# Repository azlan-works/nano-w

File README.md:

# nano-w
A tiny RP2354A based dev board with WiFi and BLE

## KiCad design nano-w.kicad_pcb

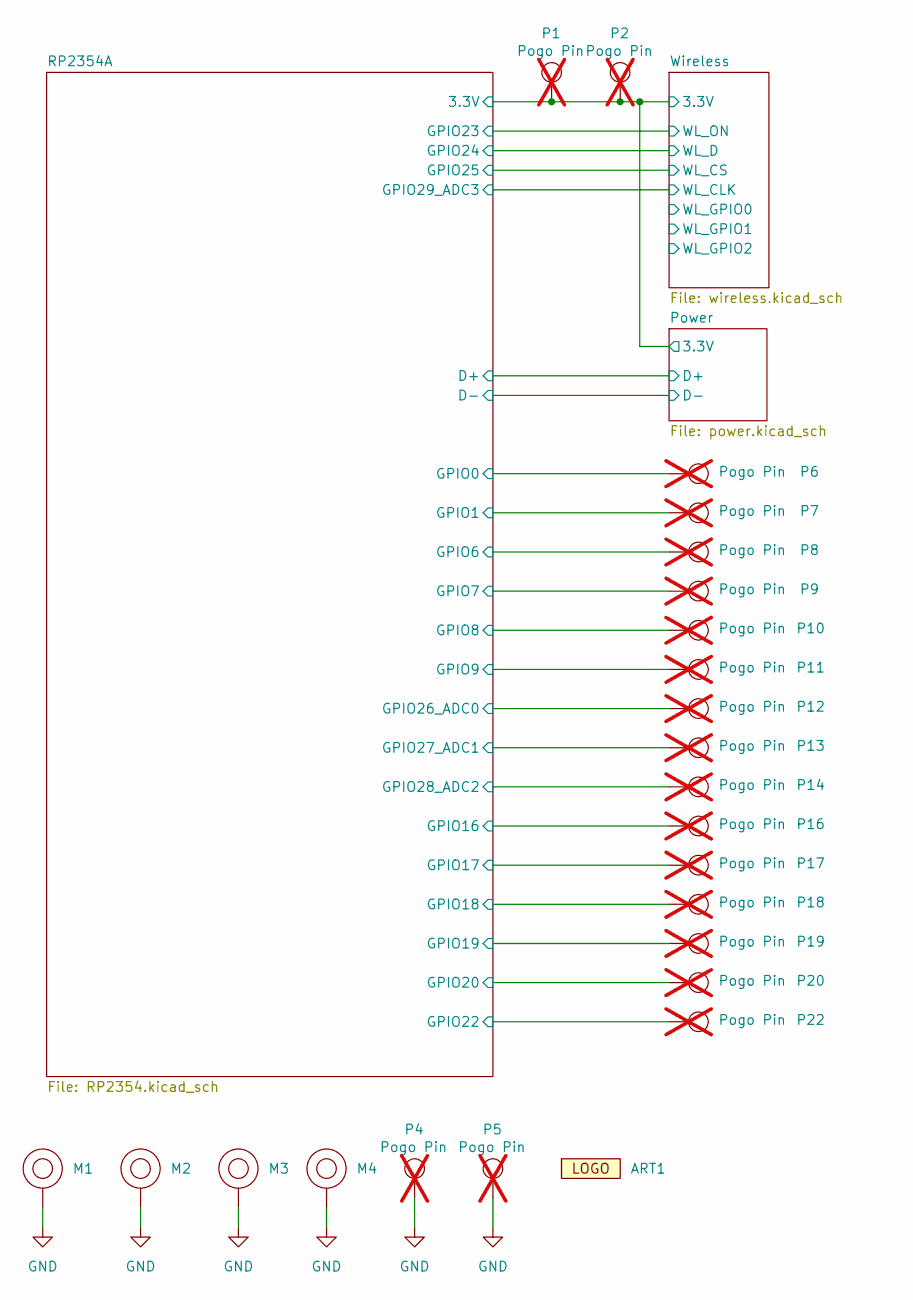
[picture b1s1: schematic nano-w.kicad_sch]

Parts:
ART1: azlan.works_logo
M1, M2, M3, M4: M2_Hole
P1, P2, P4, P5, P6, P7, P8, P9, P10, P11, P12, P13, P14, P16, P17, P18, P19, P20, P22: Pogo Pin; TESTPOINT-SMD_BD2.0_C9900030651; MPN YTC1P-3010-01; LCSC Part C5221282; not fitted

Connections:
+3V3: P1.1 (1_1), P2.1 (1_1); also elsewhere on the board
/RP2354A/GPIO6: P8.1 (1_1); also elsewhere on the board
/RP2354A/GPIO7: P9.1 (1_1); also elsewhere on the board
/RP2354A/GPIO8: P10.1 (1_1); also elsewhere on the board
/RP2354A/GPIO9: P11.1 (1_1); also elsewhere on the board
/RP2354A/GPIO16: P16.1 (1_1); also elsewhere on the board
/RP2354A/GPIO17: P17.1 (1_1); also elsewhere on the board
/RP2354A/GPIO18: P18.1 (1_1); also elsewhere on the board
/RP2354A/GPIO19: P19.1 (1_1); also elsewhere on the board
/RP2354A/GPIO20: P20.1 (1_1); also elsewhere on the board
/RP2354A/GPIO22: P22.1 (1_1); also elsewhere on the board
/RP2354A/GPIO26_ADC0: P12.1 (1_1); also elsewhere on the board
/RP2354A/GPIO27_ADC1: P13.1 (1_1); also elsewhere on the board
/RP2354A/GPIO28_ADC2: P14.1 (1_1); also elsewhere on the board
GND: M1.1 (1_1), M2.1 (1_1), M3.1 (1_1), M4.1 (1_1), P4.1 (1_1), P5.1 (1_1); also elsewhere on the board

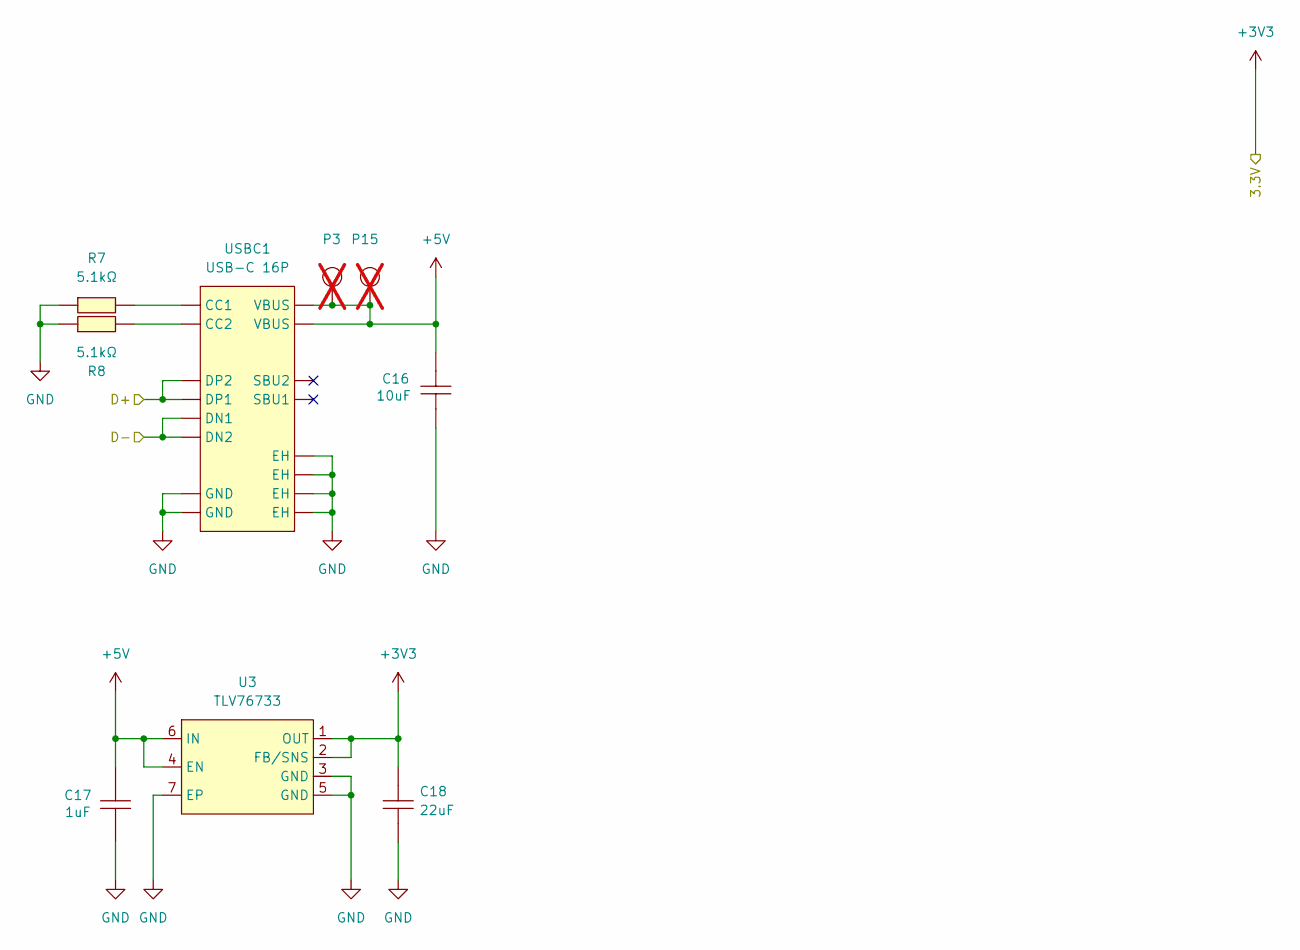
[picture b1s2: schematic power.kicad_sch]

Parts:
C16: 10uF; C0603; MPN CL10A106MA8NRNC; LCSC Part C96446
C17: 1uF; C0603; MPN CL10A105KB8NNNC; LCSC Part C15849
C18: 22uF; C0603; MPN CL10A226MQ8NRNC; LCSC Part C59461
P3, P15: Pogo Pin; TESTPOINT-SMD_BD2.0_C9900030651; MPN YTC1P-3010-01; LCSC Part C5221282; not fitted
R7, R8: 5.1kΩ; R0402; MPN 0402WGF5101TCE; LCSC Part C25905
U3: TLV76733; WSON-6_L2.0-W2.0-P0.65-TL-EP; MPN TLV76733DRVR; LCSC Part C2848334
USBC1: USB-C 16P; USB-C_SMD-TYPE-C-31-M-12_1; MPN TYPE-C-31-M-12; LCSC Part C165948

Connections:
+3V3: C18.2, U3.1 (OUT), U3.2 (FB/SNS); also elsewhere on the board
+5V: C16.2, C17.2, P3.1 (1_1), P15.1 (1_1), U3.4 (EN), U3.6 (IN), USBC1.A4B9 (VBUS), USBC1.B4A9 (VBUS)
/Power/D+: USBC1.A6 (DP1), USBC1.B6 (DP2); also elsewhere on the board
/Power/D-: USBC1.A7 (DN1), USBC1.B7 (DN2); also elsewhere on the board
GND: C16.1, C17.1, C18.1, R7.1, R8.1, U3.3 (GND), U3.5 (GND), U3.7 (EP), USBC1.1 (EH), USBC1.2 (EH), USBC1.3 (EH), USBC1.4 (EH), USBC1.A1B12 (GND), USBC1.B1A12 (GND); also elsewhere on the board
unnamed: R7.2, USBC1.A5 (CC1)
unnamed: R8.2, USBC1.B5 (CC2)

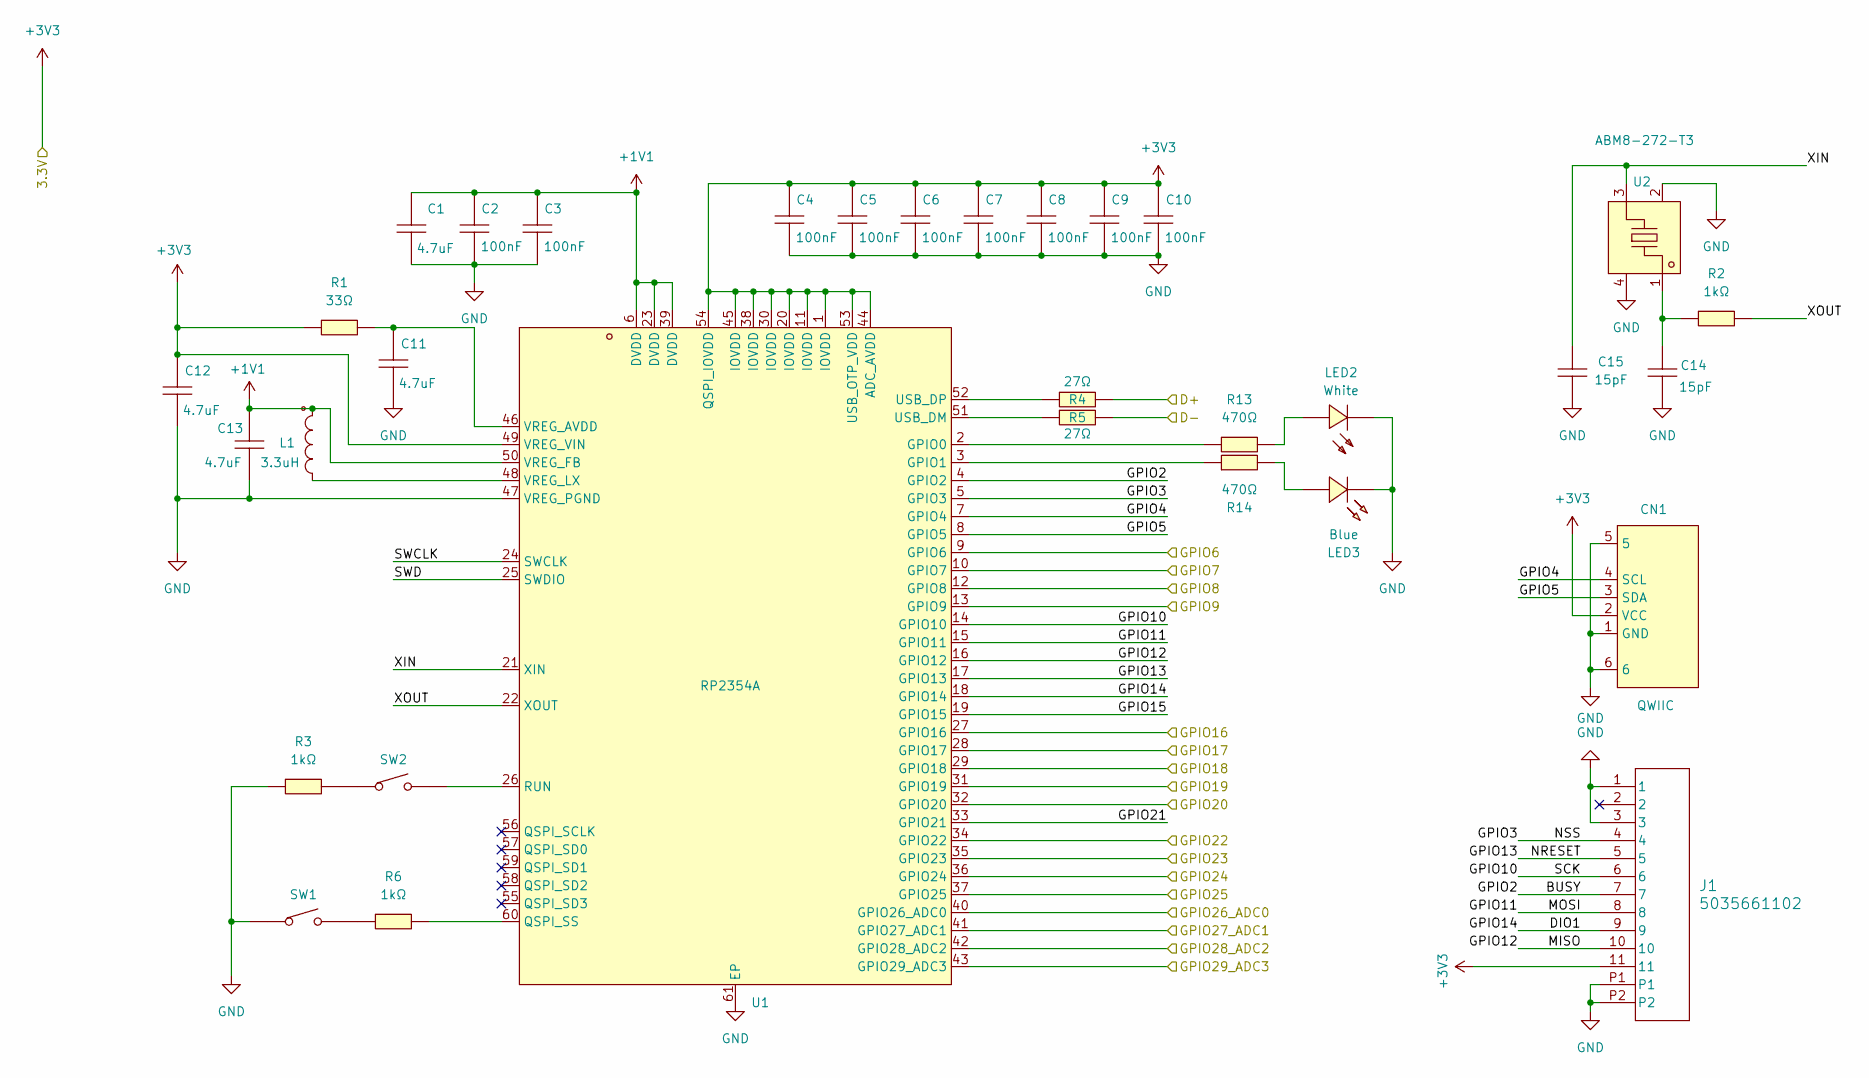
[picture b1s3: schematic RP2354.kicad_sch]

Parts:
C1, C11: 4.7uF; C0402; MPN CL05A475MP5NRNC; LCSC Part C23733
C2, C3, C4, C5, C6, C7, C8, C9, C10: 100nF; C0402; MPN CL05B104KB54PNC; LCSC Part C307331
C12, C13: 4.7uF; C0402_WIDE; MPN CL05A475MP5NRNC; LCSC Part C23733
C14, C15: 15pF; C0402; MPN 0402CG150J500NT; LCSC Part C1548
CN1: QWIIC; CONN-SMD_4P-P1.00_SM04B-SRSS-TB-LF-SN; MPN SM04B-SRSS-TB(LF)(SN); LCSC Part C160404
J1: 5035661102; CON_5035661102_MOL; MPN 503566-1102; LCSC Part C3036270
L1: 3.3uH; IND-SMD_L2.0-W1.6_AOTA-B201610S3R3-101-T; MPN AOTA-B201610S3R3-101-T; LCSC Part C42411119
LED2: White; LED-SMD_L1.0-W0.5-RD_WHITE; MPN LTW-C281DS5; LCSC Part C157742
LED3: Blue; LED0402-RD_BLUE; MPN LTST-C281TBKT-5A; LCSC Part C364550
R1: 33Ω; R0402; MPN 0402WGF330JTCE; LCSC Part C25105
R2, R3, R6: 1kΩ; R0402; MPN 0402WGF1001TCE; LCSC Part C11702
R4, R5: 27Ω; R0402; MPN 0402WGF270JTCE; LCSC Part C25100
R13, R14: 470Ω; R0402; MPN 0402WGF4700TCE; LCSC Part C25117
SW1, SW2: Button; SW-SMD_L3.9-W3.0-P4.45; MPN TS-1088-AR02016; LCSC Part C720477
U1: RP2354A; QFN-60_L7.0-W7.0-P0.40-TL-EP3.4; MPN RP2354A; LCSC Part C41378174
U2: ABM8-272-T3; CRYSTAL-SMD_4P-L3.2-W2.5-BL; MPN ABM8-272-T3; LCSC Part C20625731

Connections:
+1V1: C1.2, C2.2, C3.2, C13.2, L1.1, U1.6 (DVDD), U1.23 (DVDD), U1.39 (DVDD), U1.50 (VREG_FB)
+3V3: C4.2, C5.2, C6.2, C7.2, C8.2, C9.2, C10.2, C12.2, CN1.2 (VCC), J1.11, R1.1, U1.1 (IOVDD), U1.11 (IOVDD), U1.20 (IOVDD), U1.30 (IOVDD), U1.38 (IOVDD), U1.44 (ADC_AVDD), U1.45 (IOVDD), U1.49 (VREG_VIN), U1.53 (USB_OTP_VDD), U1.54 (QSPI_IOVDD); also elsewhere on the board
/Power/D+: R4.2; also elsewhere on the board
/Power/D-: R5.2; also elsewhere on the board
/RP2354A/BUSY: J1.7, U1.4 (GPIO2)
/RP2354A/DIO1: J1.9, U1.18 (GPIO14)
/RP2354A/GPIO3: J1.4, U1.5 (GPIO3)
/RP2354A/GPIO4: CN1.4 (SCL), U1.7 (GPIO4)
/RP2354A/GPIO5: CN1.3 (SDA), U1.8 (GPIO5)
/RP2354A/GPIO6: U1.9 (GPIO6); also elsewhere on the board
/RP2354A/GPIO7: U1.10 (GPIO7); also elsewhere on the board
/RP2354A/GPIO8: U1.12 (GPIO8); also elsewhere on the board
/RP2354A/GPIO9: U1.13 (GPIO9); also elsewhere on the board
/RP2354A/GPIO10: J1.6, U1.14 (GPIO10)
/RP2354A/GPIO11: J1.8, U1.15 (GPIO11)
/RP2354A/GPIO12: J1.10, U1.16 (GPIO12)
/RP2354A/GPIO13: J1.5, U1.17 (GPIO13)
/RP2354A/GPIO15: U1.19 (GPIO15)
/RP2354A/GPIO16: U1.27 (GPIO16); also elsewhere on the board
/RP2354A/GPIO17: U1.28 (GPIO17); also elsewhere on the board
/RP2354A/GPIO18: U1.29 (GPIO18); also elsewhere on the board
/RP2354A/GPIO19: U1.31 (GPIO19); also elsewhere on the board
/RP2354A/GPIO20: U1.32 (GPIO20); also elsewhere on the board
/RP2354A/GPIO21: U1.33 (GPIO21)
/RP2354A/GPIO22: U1.34 (GPIO22); also elsewhere on the board
/RP2354A/GPIO23: U1.35 (GPIO23); also elsewhere on the board
/RP2354A/GPIO24: U1.36 (GPIO24); also elsewhere on the board
/RP2354A/GPIO25: U1.37 (GPIO25); also elsewhere on the board
/RP2354A/GPIO26_ADC0: U1.40 (GPIO26_ADC0); also elsewhere on the board
/RP2354A/GPIO27_ADC1: U1.41 (GPIO27_ADC1); also elsewhere on the board
/RP2354A/GPIO28_ADC2: U1.42 (GPIO28_ADC2); also elsewhere on the board
/RP2354A/GPIO29_ADC3: U1.43 (GPIO29_ADC3); also elsewhere on the board
/RP2354A/SWCLK: U1.24 (SWCLK)
/RP2354A/SWD: U1.25 (SWDIO)
/RP2354A/XIN: C15.1, U1.21 (XIN), U2.3
/RP2354A/XOUT: R2.2, U1.22 (XOUT)
GND: C1.1, C2.1, C3.1, C4.1, C5.1, C6.1, C7.1, C8.1, C9.1, C10.1, C11.1, C12.1, C13.1, C14.2, C15.2, CN1.1 (GND), CN1.5, CN1.6, J1.1, J1.3, J1.P1, J1.P2, LED2.1 (-), LED3.1 (K), R3.1, SW1.1, U1.47 (VREG_PGND), U1.61 (EP), U2.2 (GND), U2.4 (GND); also elsewhere on the board
unnamed: C14.1, R2.1, U2.1
unnamed: LED2.2 (+), R13.2
unnamed: LED3.2 (A), R14.2
unnamed: R3.2, SW2.1
unnamed: R6.1, SW1.2
unnamed: R13.1, U1.2 (GPIO0)
unnamed: R14.1, U1.3 (GPIO1)
unnamed: R6.2, U1.60 (QSPI_SS)
unnamed: SW2.2, U1.26 (RUN)
unnamed: R5.1, U1.51 (USB_DM)
unnamed: R4.1, U1.52 (USB_DP)
unnamed: C11.2, R1.2, U1.46 (VREG_AVDD)
unnamed: L1.2, U1.48 (VREG_LX)

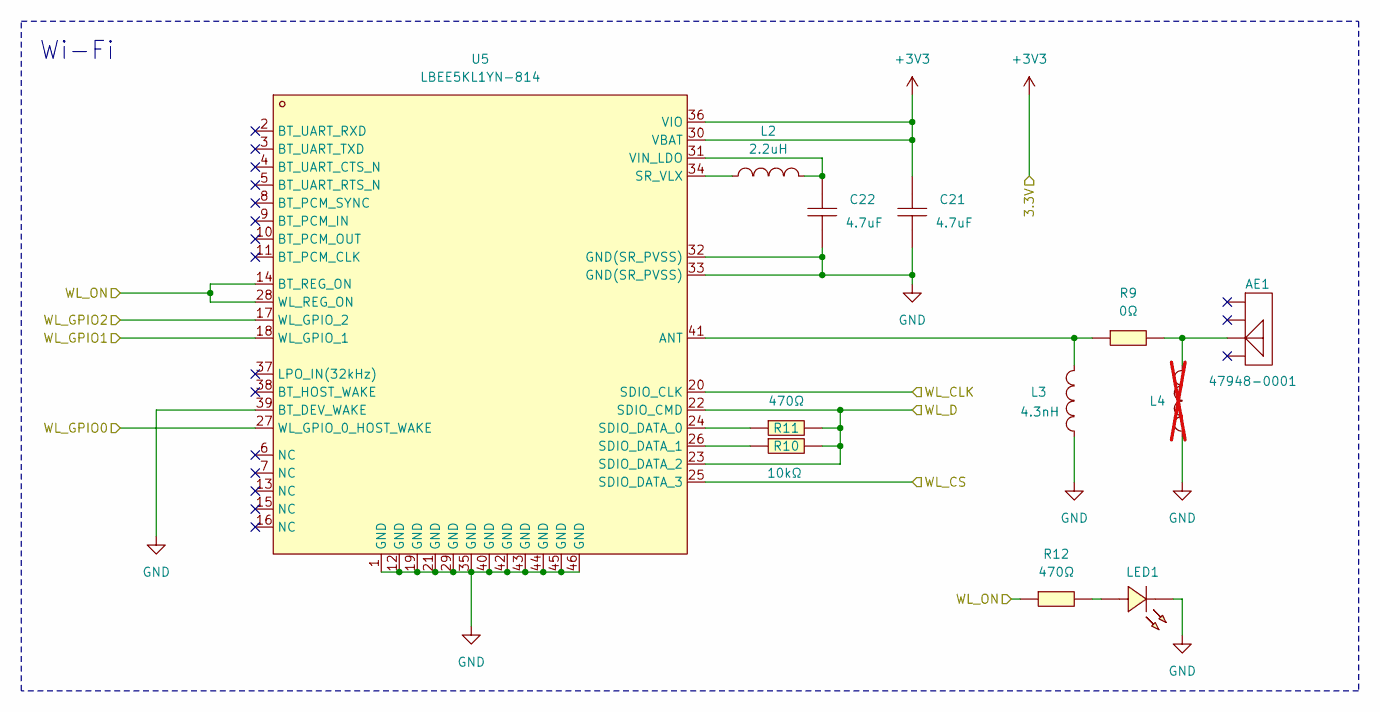
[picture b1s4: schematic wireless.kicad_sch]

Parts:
AE1: 47948-0001; ANT-SMD_47948-0001; MPN 47948-0001; LCSC Part C152351
C21, C22: 4.7uF; C0402; MPN CL05A475MP5NRNC; LCSC Part C23733
L2: 2.2uH; L0603; MPN LQM18PN2R2MFRL; LCSC Part C337910
L3: 4.3nH; L0402-RD; MPN MLG1005S4N3CT000; LCSC Part C275290
L4: 4.3nH; L0402-RD; MPN MLG1005S4N3CT000; LCSC Part C275290; not fitted
LED1: LTST-C281TGKT-5A; LED0402-R-RD_GREEN; MPN LTST-C281TGKT-5A; LCSC Part C364549
R9: 0Ω; R0402; MPN 0402WGF0000TCE; LCSC Part C17168
R10: 10kΩ; R0402; MPN 0402WGF1002TCE; LCSC Part C25744
R11, R12: 470Ω; R0402; MPN 0402WGF4700TCE; LCSC Part C25117
U5: LBEE5KL1YN-814; LGA-46_L7.0-W5.2_LBEE5KL1DX-883; MPN LBEE5KL1YN-814; LCSC Part C6583742

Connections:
+3V3: C21.2, U5.30 (VBAT), U5.36 (VIO); also elsewhere on the board
/RP2354A/GPIO23: R12.1, U5.14 (BT_REG_ON), U5.28 (WL_REG_ON); also elsewhere on the board
/RP2354A/GPIO24: R10.2, R11.2, U5.22 (SDIO_CMD), U5.23 (SDIO_DATA_2); also elsewhere on the board
/RP2354A/GPIO25: U5.25 (SDIO_DATA_3); also elsewhere on the board
/RP2354A/GPIO29_ADC3: U5.20 (SDIO_CLK); also elsewhere on the board
/Wireless/WL_GPIO0: U5.27 (WL_GPIO_0_HOST_WAKE)
/Wireless/WL_GPIO1: U5.18 (WL_GPIO_1)
/Wireless/WL_GPIO2: U5.17 (WL_GPIO_2)
GND: C21.1, C22.1, L3.2, L4.2, LED1.2 (K), U5.1 (GND), U5.12 (GND), U5.19 (GND), U5.21 (GND), U5.29 (GND), U5.32 (GND(SR_PVSS)), U5.33 (GND(SR_PVSS)), U5.35 (GND), U5.39 (BT_DEV_WAKE), U5.40 (GND), U5.42 (GND), U5.43 (GND), U5.44 (GND), U5.45 (GND), U5.46 (GND); also elsewhere on the board
unnamed: AE1.3 (3_3), L4.1, R9.2
unnamed: LED1.1 (A), R12.2
unnamed: L3.1, R9.1, U5.41 (ANT)
unnamed: R11.1, U5.24 (SDIO_DATA_0)
unnamed: R10.1, U5.26 (SDIO_DATA_1)
unnamed: L2.2, U5.34 (SR_VLX)
unnamed: C22.2, L2.1, U5.31 (VIN_LDO)

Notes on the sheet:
Wi-Fi

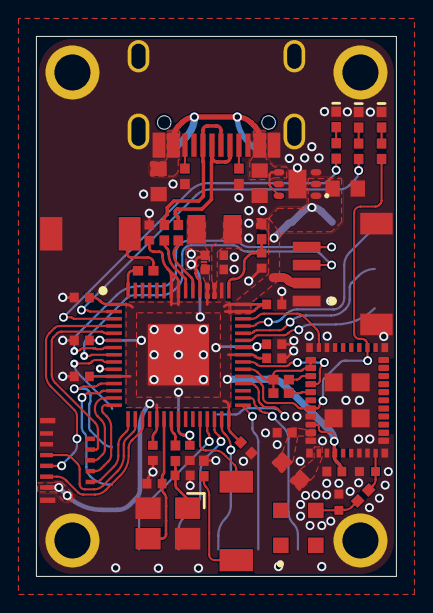
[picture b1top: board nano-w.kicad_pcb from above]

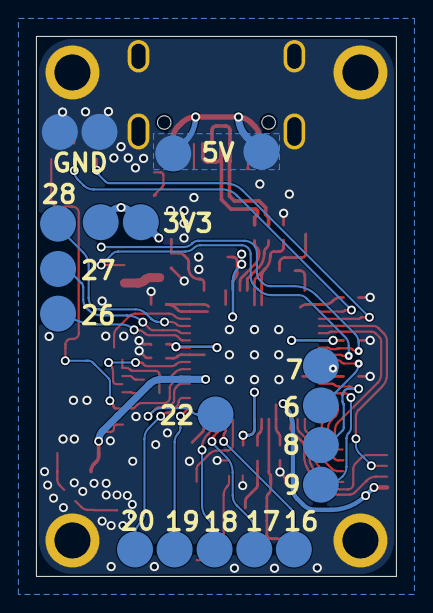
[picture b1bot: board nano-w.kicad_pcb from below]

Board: 4 copper layers, 20.0 x 30.0 mm, 76 parts (20 on the bottom side), 56 nets.

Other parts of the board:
ART1#2: azlan.works_logo

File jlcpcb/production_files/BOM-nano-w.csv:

Comment,Designator,Footprint,LCSC,Quantity
0Ω,R9,R0402,C17168,1
100nF,"C10,C2,C3,C4,C5,C6,C7,C8,C9",C0402,C307331,9
10kΩ,R10,R0402,C25744,1
10uF,C16,C0603,C96446,1
15pF,"C14,C15",C0402,C1548,2
1kΩ,"R2,R3,R6",R0402,C11702,3
1uF,C17,C0603,C15849,1
2.2uH,L2,L0603,C337910,1
22uF,C18,C0603,C59461,1
27Ω,"R4,R5",R0402,C25100,2
3.3uH,L1,IND-SMD_L2.0-W1.6_AOTA-B201610S3R3-101-T,C42411119,1
33Ω,R1,R0402,C25105,1
4.3nH,L3,L0402-RD,C275290,1
4.7uF,"C1,C11,C12,C13,C21,C22",C0402,C23733,6
470Ω,"R11,R12,R13,R14",R0402,C25117,4
47948-0001,AE1,ANT-SMD_47948-0001,C152351,1
5.1kΩ,"R7,R8",R0402,C25905,2
5035661102,J1,CON_5035661102_MOL,C3036270,1
ABM8-272-T3,U2,CRYSTAL-SMD_4P-L3.2-W2.5-BL,C20625731,1
Blue,LED3,LED0402-RD_BLUE,C364550,1
Button,"SW1,SW2",SW-SMD_L3.9-W3.0-P4.45,C720477,2
LBEE5KL1YN-814,U5,LGA-46_L7.0-W5.2_LBEE5KL1DX-883,C6583742,1
LTST-C281TGKT-5A,LED1,LED0402-R-RD_GREEN,C364549,1
QWIIC,CN1,CONN-SMD_4P-P1.00_SM04B-SRSS-TB-LF-SN,C160404,1
RP2354A,U1,QFN-60_L7.0-W7.0-P0.40-TL-EP3.4,C41378174,1
TLV76733,U3,WSON-6_L2.0-W2.0-P0.65-TL-EP,C2848334,1
USB-C 16P,USBC1,USB-C_SMD-TYPE-C-31-M-12_1,C165948,1
White,LED2,LED-SMD_L1.0-W0.5-RD_WHITE,C157742,1
~,ART1,azlan.works_logo,,1
